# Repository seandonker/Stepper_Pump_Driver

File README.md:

# Stepper Pump Driver
Kicad design files and C code (adding soon) for a small PCB to control a peristaltic stepper motor pump (or any single low current bipolar stepper really).

This project was created as a cheaper alternative for fully integrated peristaltic pump solutions that tend to cost $200 or more. These stand alone units use pumps that can be had for ~$50 and lack the full programmability that this project offers through Arduino coding. While this project was meant to be used for controllings pumps (like 
[this pump here](https://www.amazon.ca/Peristaltic-Stepper-Kamoer-KPHM400-Variable/dp/B097XXJ1XD/ref=sr_1_6?crid=3FM26AUWYPZCK&keywords=peristaltic+stepper&qid=1704066873&sprefix=%2Caps%2C176&sr=8-6)), it can be used for a variety of purposes where some adjustments need to be made on the fly by someone who may not know how to program/flash the arduino. This is why the design features a potentiometer and a button to change things like speed or on-time intervals. 

Component Requirements
---------------------
Apart from the provided BOM and Digikey list. The system needs a power supply, stepper motor, and the display purchased separately. 
* The power supply jack is a standard 2.1mmID x 5.5mmOD size and the supply should be rated for 12v and 3 amps or greater. 
* Bipolar stepper motor (currently selected plug socket is for a JST XHP-4 and max motor current is 1A RMS)
* The OLED display is a common 0.91" I2C with a SSD1306 chipset used in Arduino projects
* The USB differential lines were designed for a 1mm thick, 1oz top and bottom, 2-layer board (I ordered from JLPCB)

[Digikey List](https://www.digikey.ca/en/mylists/list/M6HG9QW1PJ)

Programming and Power
---------------------
The board uses the common ATMEGA328P found in some standard models of Arduinos as this allows for the use of the libraries created for the OLED screen saving a lot of time and effort. 
There is an in-circuit-serial-programming (ICSP) header to burn the arduino bootloader if the chips were purchased blank from a distributor. Then you can either continue using the header for programming or use the USB port. For the USB to work however, the USB host controller chip (FT230X) needs to be programmed through the FT_PROG utility to change one output signal of the device. Please check the schematic and the datasheet of the chip for more details. The motor driver can only be powered from the 12v source but the MCU can run from either the USB or the 12v adapter allowing for programming without the 12v supply. Both can be plugged in simultaneously without issue for serial communication for data logging or other purposes. 

Future Improvements
------------------
I would like to use a 5v regulator capable of higher input voltages (or use a DC-DC converter) so the motor controller is capable of higher speeds. With that, it would be better if the PCB has 2oz copper layers for more current and better heat sinking capabilities. This would likely require a 4-layer board however as the USB trace impedance would become hard to design. A rotary encoder would be a much better method of input too, and would be easy to implement in hardware with a 4-layer board (but would require slightly more programming).

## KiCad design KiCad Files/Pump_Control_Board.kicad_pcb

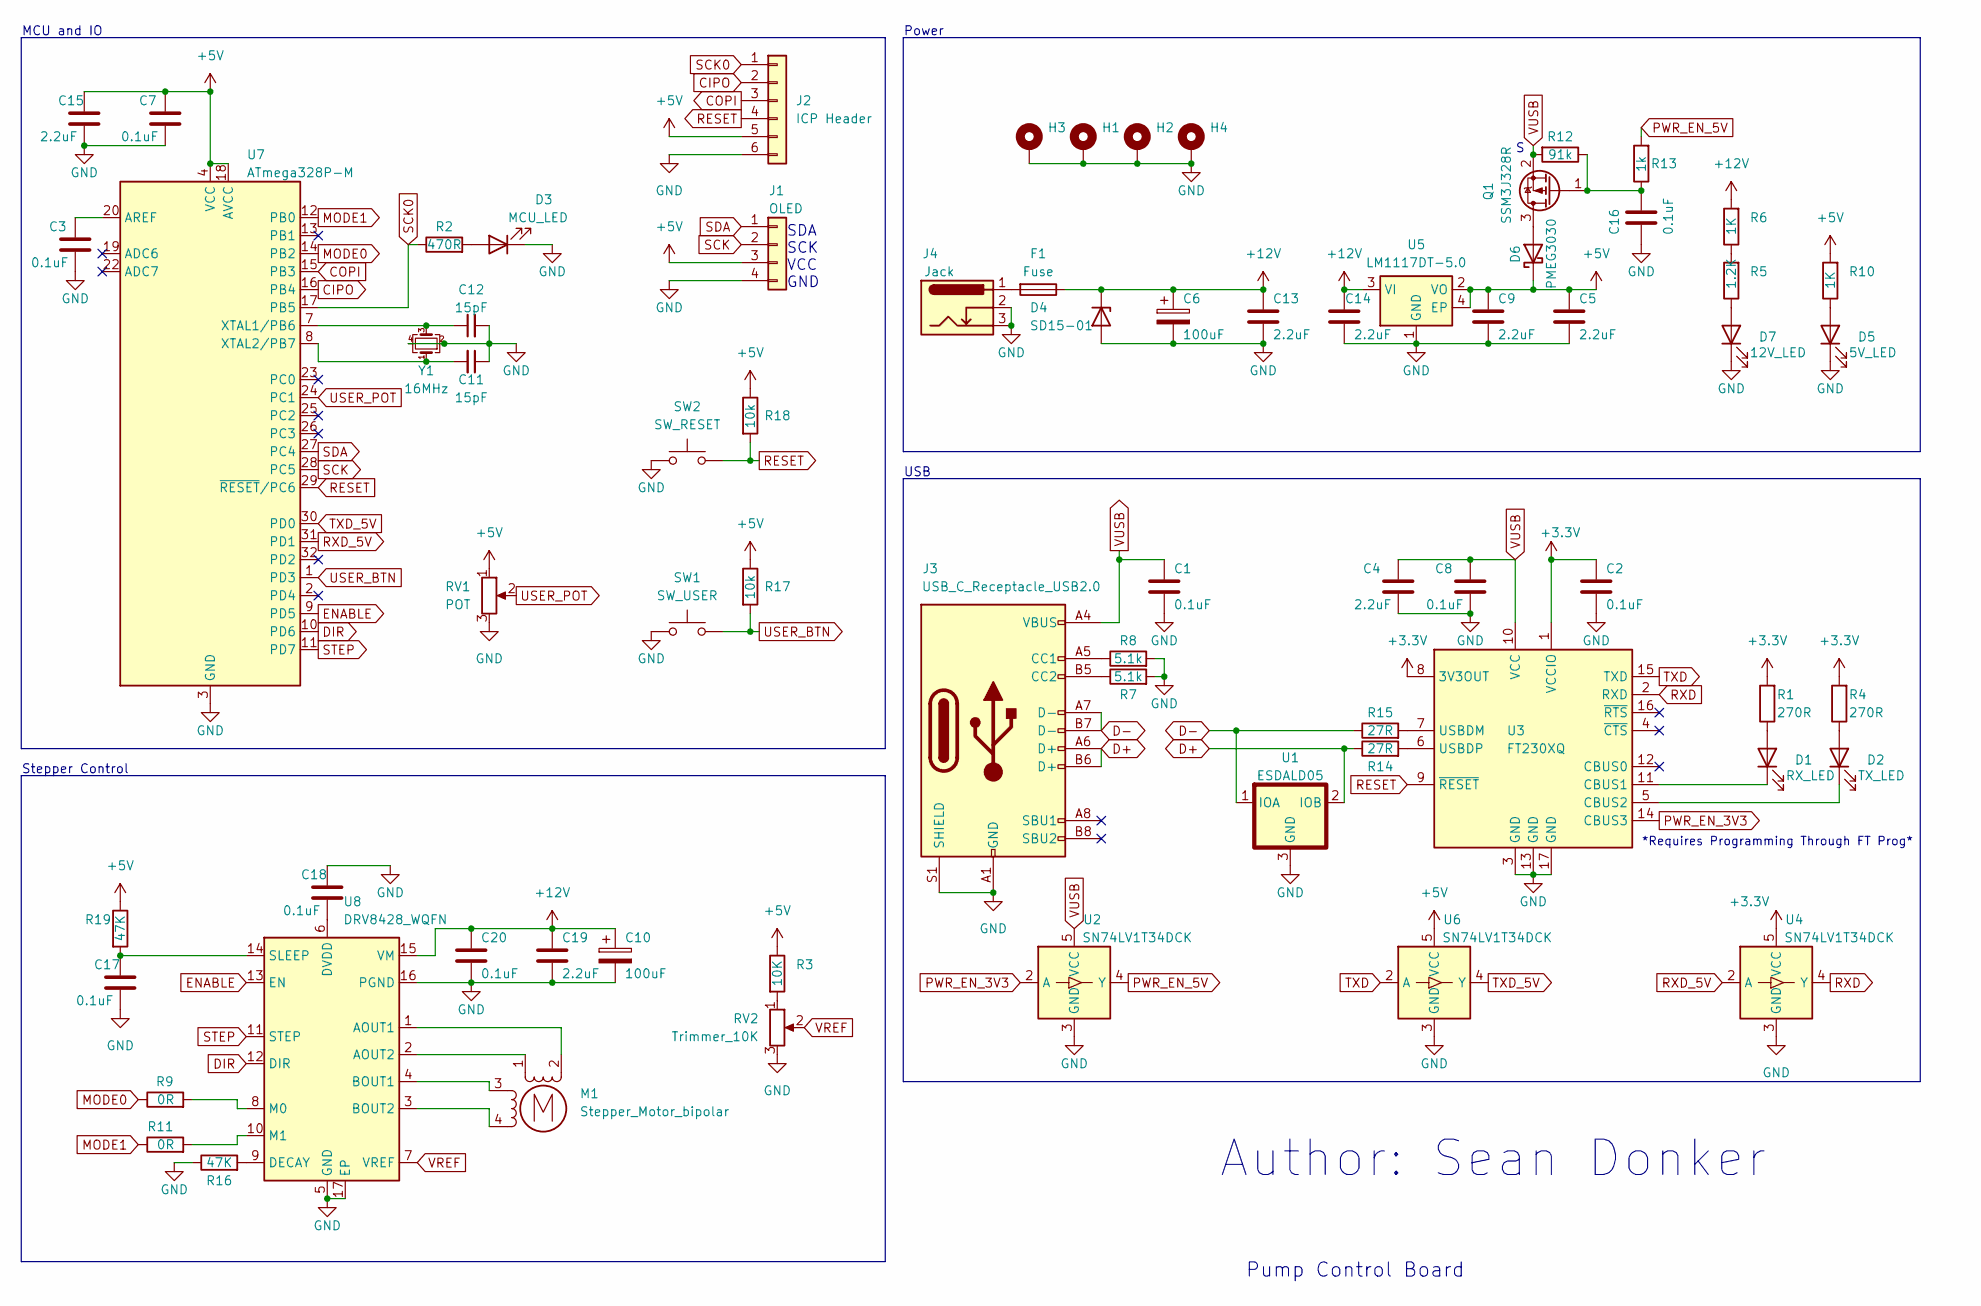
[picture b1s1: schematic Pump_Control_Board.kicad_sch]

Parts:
C1, C2, C3, C7, C8, C16, C17, C18, C20: 0.1uF; C_0603_1608Metric_Pad1.08x0.95mm_HandSolder
C4, C5, C9, C13, C14, C15, C19: 2.2uF; C_0603_1608Metric_Pad1.08x0.95mm_HandSolder
C6, C10: 100uF; CP_Radial_D4.0mm_P2.00mm
C11, C12: 15pF; C_0402_1005Metric_Pad0.74x0.62mm_HandSolder
D1: RX_LED; LED_0805_2012Metric_Pad1.15x1.40mm_HandSolder
D2: TX_LED; LED_0805_2012Metric_Pad1.15x1.40mm_HandSolder
D3: MCU_LED; LED_0805_2012Metric_Pad1.15x1.40mm_HandSolder
D4: SD15-01; D_SOD-323F
D5: 5V_LED; LED_0805_2012Metric_Pad1.15x1.40mm_HandSolder
D6: PMEG3030; D_SOD-128
D7: 12V_LED; LED_0805_2012Metric_Pad1.15x1.40mm_HandSolder
F1: Fuse; Fuse_1206_3216Metric_Pad1.42x1.75mm_HandSolder
H1, H2, H3, H4: MountingHole_Pad; MountingHole_3.2mm_M3_ISO7380_Pad_TopBottom
J1: OLED; PinSocket_1x04_P2.54mm_Vertical
J2: ICP Header; PinHeader_1x06_P2.54mm_Vertical
J3: USB_C_Receptacle_USB2.0; USB_C_Receptacle_GCT_USB4085
J4: Jack; BarrelJack_GCT_DCJ200-10-A_Horizontal
M1: Stepper_Motor_bipolar; JST_XH_B4B-XH-A_1x04_P2.50mm_Vertical
Q1: SSM3J328R; SOT-23
R1, R4: 270R; R_0603_1608Metric_Pad0.98x0.95mm_HandSolder
R2: 470R; R_0603_1608Metric_Pad0.98x0.95mm_HandSolder
R3: 10K; R_0603_1608Metric_Pad0.98x0.95mm_HandSolder
R5: 1.2K; R_0603_1608Metric_Pad0.98x0.95mm_HandSolder
R6, R10: 1K; R_0603_1608Metric_Pad0.98x0.95mm_HandSolder
R7, R8: 5.1k; R_0603_1608Metric_Pad0.98x0.95mm_HandSolder
R9, R11: 0R; R_0402_1005Metric
R12: 91k; R_0603_1608Metric_Pad0.98x0.95mm_HandSolder
R13: 1k; R_0603_1608Metric_Pad0.98x0.95mm_HandSolder
R14, R15: 27R; R_0402_1005Metric_Pad0.72x0.64mm_HandSolder
R16, R19: 47K; R_0603_1608Metric_Pad0.98x0.95mm_HandSolder
R17, R18: 10k; R_0603_1608Metric_Pad0.98x0.95mm_HandSolder
RV1: POT; Potentiometer_Bourns_PTV09A-1_Single_Vertical
RV2: Trimmer_10K; Potentiometer_Bourns_TC33X_Vertical
SW1: SW_USER; SW_PUSH-12mm
SW2: SW_RESET; SW_PUSH_6mm
U1: ESDALD05; SOT-23-3
U2, U4, U6: SN74LV1T34DCK; SOT-353_SC-70-5
U3: FT230XQ; QFN-16-1EP_4x4mm_P0.65mm_EP2.1x2.1mm
U5: LM1117DT-5.0; SOT-223
U7: ATmega328P-M; QFN-32-1EP_5x5mm_P0.5mm_EP3.1x3.1mm
U8: DRV8428_WQFN; WQFN-16-1EP_3x3mm_P0.5mm_EP1.68x1.68mm
Y1: 16MHz; Crystal_SMD_3225-4Pin_3.2x2.5mm

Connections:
+3.3V: C2.1, R1.2, R4.2, U3.1 (VCCIO), U3.8 (3V3OUT), U4.5 (VCC)
+5V: C5.1, C7.1, C9.1, C15.1, D6.1 (K), J1.3, J2.5, R3.1, R10.2, R17.1, R18.1, R19.1, RV1.1, U5.2 (VO), U5.4 (EP), U6.5 (VCC), U7.4 (VCC), U7.6 (VCC), U7.18 (AVCC)
+12V: C6.1, C10.1, C13.1, C14.1, C19.1, C20.1, D4.1 (K), F1.1, R6.2, U5.3 (VI), U8.15 (VM)
CIPO: J2.2, U7.16 (PB4)
COPI: J2.3, U7.15 (PB3)
D+: J3.A6 (D+), J3.B6 (D+), R14.1, U1.2 (IOB)
D-: J3.A7 (D-), J3.B7 (D-), R15.1, U1.1 (IOA)
DIR: U7.10 (PD6), U8.12 (DIR)
ENABLE: U7.9 (PD5), U8.13 (EN)
GND: C1.2, C2.2, C3.2, C4.2, C5.2, C6.2, C7.2, C8.2, C9.2, C10.2, C11.1, C12.2, C13.2, C14.2, C15.2, C16.2, C17.2, C18.1, C19.2, C20.2, D3.1 (K), D4.2 (A), D5.1 (K), D7.1 (K), H1.1, H2.1, H3.1, H4.1, J1.4, J2.6, J3.A1 (GND), J3.A12 (GND), J3.B1 (GND), J3.B12 (GND), J3.S1 (SHIELD), J4.2, J4.3, R7.2, R8.2, R16.1, RV1.3, RV2.3, SW1.1, SW2.1, U1.3 (GND), U2.3 (GND), U3.3 (GND), U3.13 (GND), U3.17 (GND), U4.3 (GND), U5.1 (GND), U6.3 (GND), U7.3 (GND), U7.5 (GND), U7.21 (GND), U7.33 (GND), U8.5 (GND), U8.16 (PGND), U8.17 (EP), Y1.2, Y1.4
MODE0: R9.1, U7.14 (PB2)
MODE1: R11.1, U7.12 (PB0)
unnamed: D1.2 (A), R1.1
unnamed: D1.1 (K), U3.11 (CBUS1)
unnamed: D2.2 (A), R4.1
unnamed: D2.1 (K), U3.5 (CBUS2)
unnamed: D3.2 (A), R2.2
unnamed: D5.2 (A), R10.1
unnamed: D6.2 (A), Q1.3 (D)
unnamed: D7.2 (A), R5.1
unnamed: F1.2, J4.1
unnamed: J3.A5 (CC1), R8.1
unnamed: J3.B5 (CC2), R7.1
unnamed: M1.2 (-), U8.1 (AOUT1)
unnamed: C16.1, Q1.1 (G), R12.1, R13.1
unnamed: R3.2, RV2.1
unnamed: R5.2, R6.1
unnamed: R15.2, U3.7 (USBDM)
unnamed: R14.2, U3.6 (USBDP)
unnamed: C3.1, U7.20 (AREF)
unnamed: C12.1, U7.7 (XTAL1/PB6), Y1.3
unnamed: C11.2, U7.8 (XTAL2/PB7), Y1.1
unnamed: M1.1, U8.2 (AOUT2)
unnamed: M1.3, U8.4 (BOUT1)
unnamed: M1.4, U8.3 (BOUT2)
unnamed: R16.2, U8.9 (DECAY)
unnamed: C18.2, U8.6 (DVDD)
unnamed: R9.2, U8.8 (M0)
unnamed: R11.2, U8.10 (M1)
unnamed: C17.1, R19.2, U8.14 (SLEEP)
PWR_EN_3V3: U2.2 (A), U3.14 (CBUS3)
PWR_EN_5V: R13.2, U2.4 (Y)
RESET: J2.4, R18.2, SW2.2, U3.9 (~RESET), U7.29 (~RESET/PC6)
RXD: U3.2 (RXD), U4.4 (Y)
RXD_5V: U4.2 (A), U7.31 (PD1)
SCK: J1.2, U7.28 (PC5)
SCK0: J2.1, R2.1, U7.17 (PB5)
SDA: J1.1, U7.27 (PC4)
STEP: U7.11 (PD7), U8.11 (STEP)
TXD: U3.15 (TXD), U6.2 (A)
TXD_5V: U6.4 (Y), U7.30 (PD0)
USER_BTN: R17.2, SW1.2, U7.1 (PD3)
USER_POT: RV1.2, U7.24 (PC1)
VREF: RV2.2, U8.7 (VREF)
VUSB: C1.1, C4.1, C8.1, J3.A4 (VBUS), J3.A9 (VBUS), J3.B4 (VBUS), J3.B9 (VBUS), Q1.2 (S), R12.2, U2.5 (VCC), U3.10 (VCC)

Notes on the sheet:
Author: Sean Donker
SDA SCK VCC GND
USB
MCU and IO
Stepper Control
Power
Pump Control Board
*Requires Programming Through FT Prog*

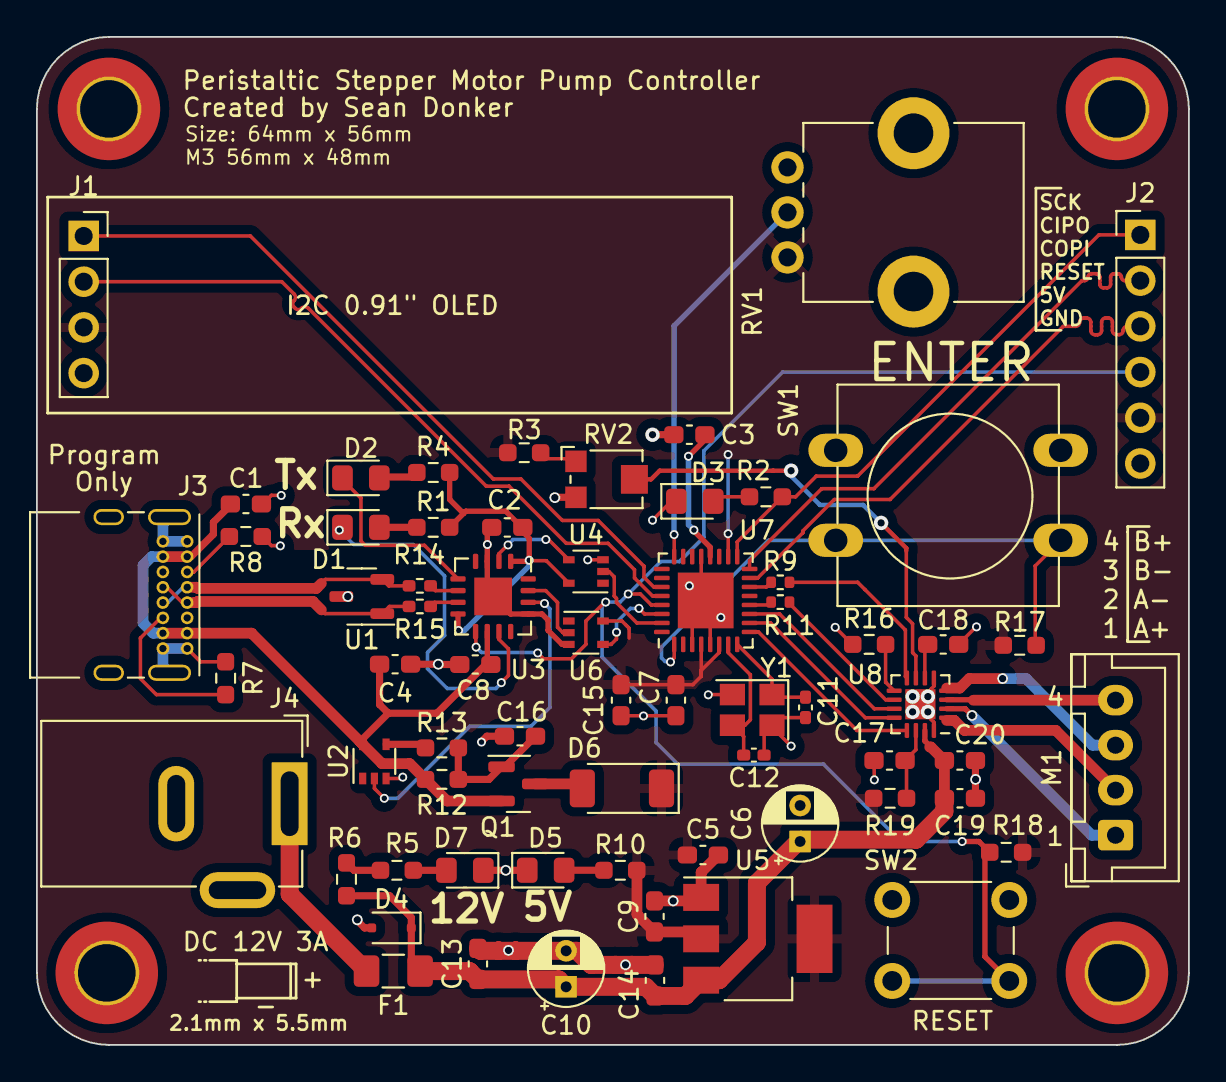
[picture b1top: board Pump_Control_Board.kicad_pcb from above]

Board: 2 copper layers, 64.0 x 56.0 mm, 70 parts (0 on the bottom side), 55 nets.

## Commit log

2023-12-31 PCB File Add
2023-12-31 Deleted duplicate Production zip
2023-12-31 Named ICP Header
2024-01-01 Updated README.md, partially complete
2024-01-03 added pcb layout pic
2024-01-03 added info about FT230X
2024-01-07 added BOM
2024-01-07 added digi list
